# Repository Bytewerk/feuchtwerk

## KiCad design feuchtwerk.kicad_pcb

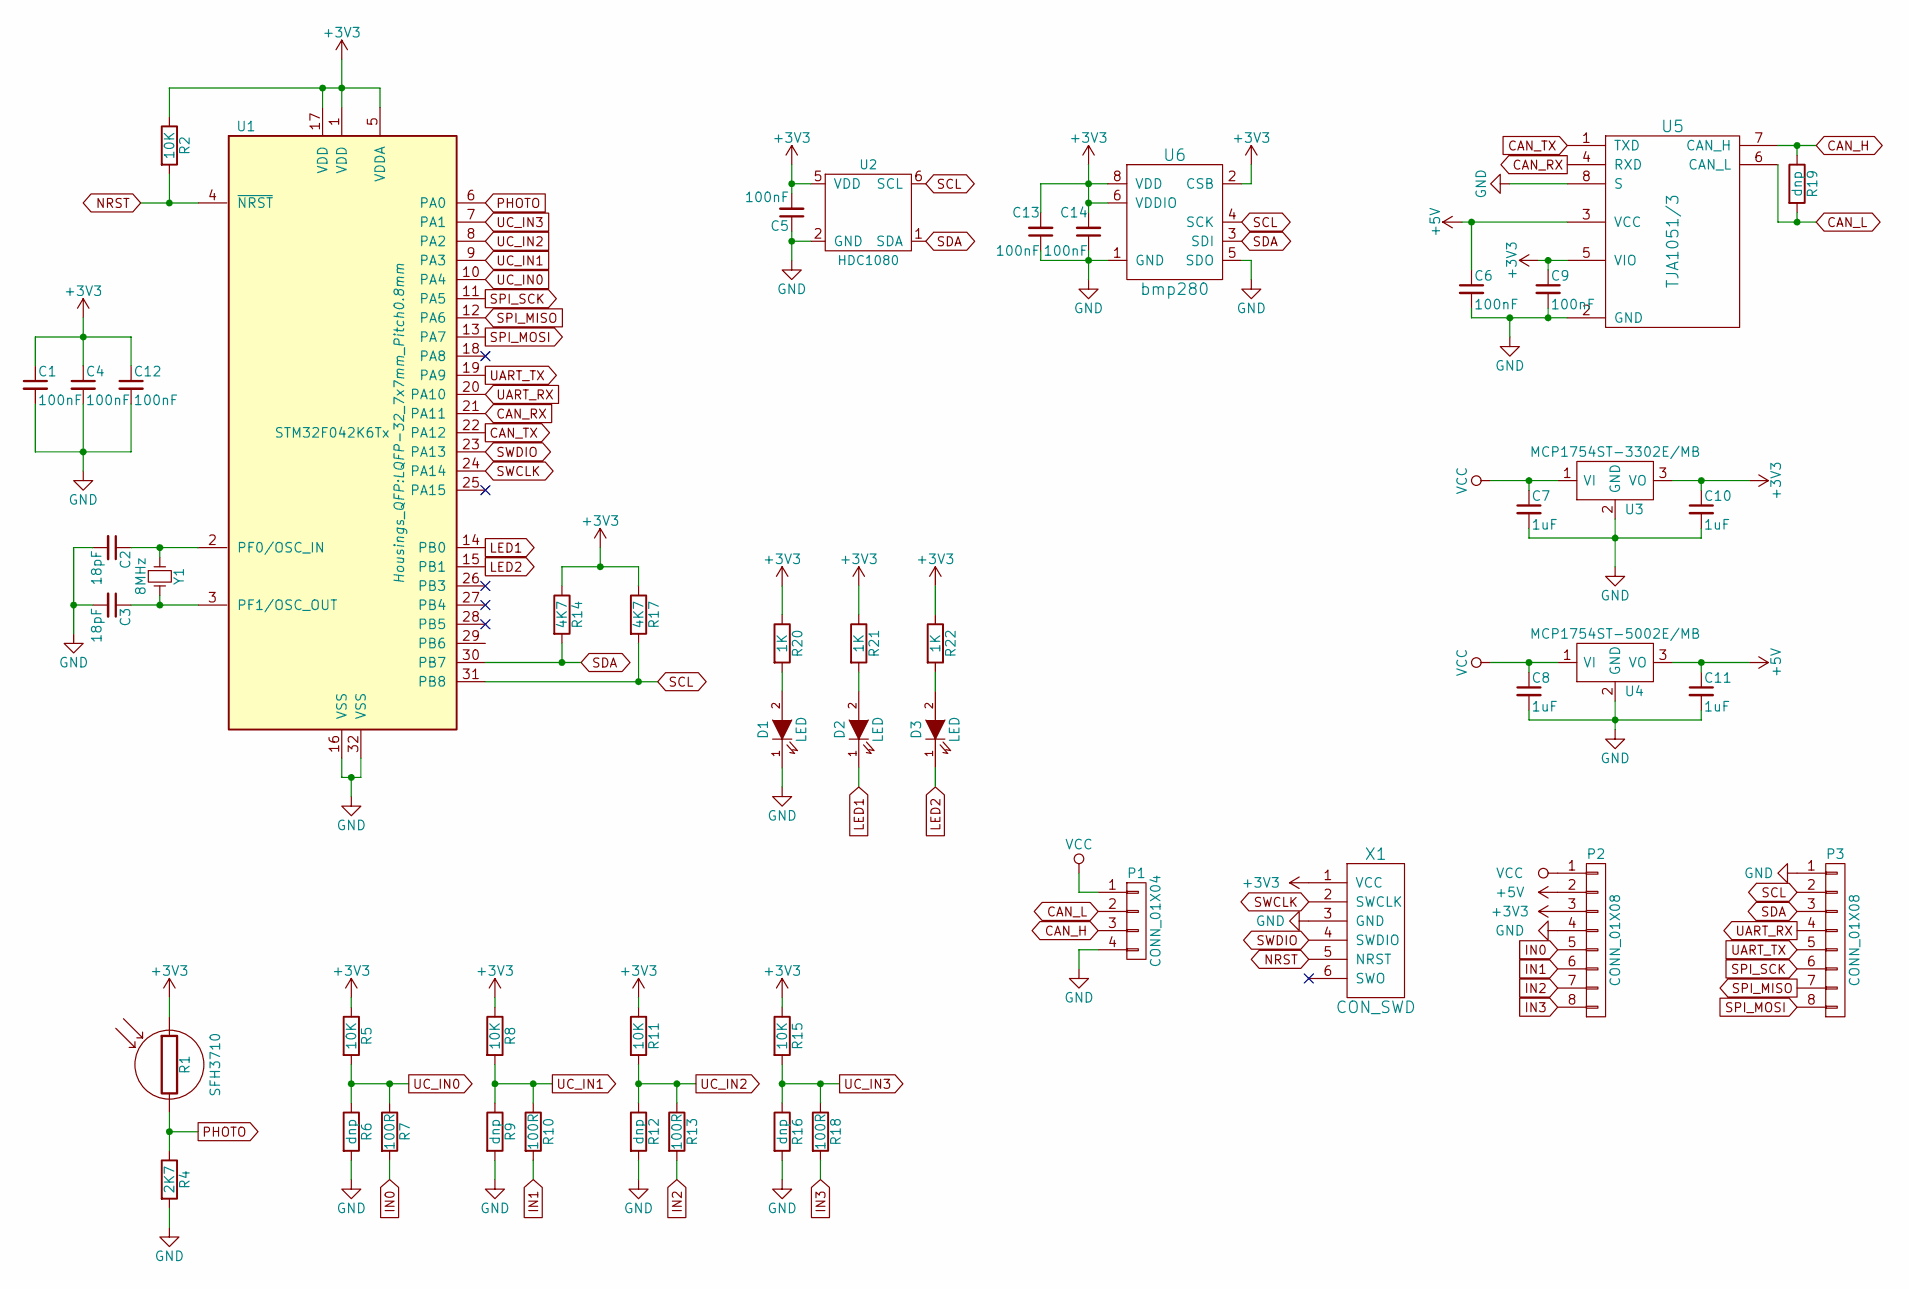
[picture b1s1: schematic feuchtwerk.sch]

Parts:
C1, C4, C5, C6, C9, C12, C13, C14: 100nF; C_0603
C2, C3: 18pF; C_0603
C7, C8, C10, C11: 1uF; C_0603
D1, D2, D3: LED; LED_0603
P1: CONN_01X04; Pin_Header_Straight_1x04
P2, P3: CONN_01X08; Pin_Header_Straight_1x08
R1: SFH3710; R_1206
R2, R5, R8, R11, R15: 10K; R_0603
R4: 2K7; R_0603
R6, R9, R12, R16: dnp; R_0603
R7, R10, R13, R18: 100R; R_0603
R14, R17: 4K7; R_0603
R19: dnp; R_0805
R20, R21, R22: 1K; R_0603
U1: STM32F042K6Tx; LQFP-32_7x7mm_Pitch0.8mm
U2: HDC1080; TEXAS-S-PWSON-N6
U3: MCP1754ST-3302E/MB; SOT89-3_Housing
U4: MCP1754ST-5002E/MB; SOT89-3_Housing
U5: TJA1051/3; SOIC-8_3.9x4.9mm_Pitch1.27mm
U6: bmp280
X1: CON_SWD; TC2030-NL
Y1: 8MHz; ABM3

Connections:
+3V3: C1.1, C4.1, C5.2, C9.1, C10.1, C12.1, C13.2, C14.2, P2.3, R1.1, R2.1, R5.1, R8.1, R11.1, R14.1, R15.1, R17.1, R20.1, R21.1, R22.1, U1.1 (VDD), U1.5 (VDDA), U1.17 (VDD), U2.5 (VDD), U3.3 (VO), U5.5 (VIO), U6.2 (CSB), U6.6 (VDDIO), U6.8 (VDD), X1.1 (VCC)
+5V: C6.1, C11.1, P2.2, U4.3 (VO), U5.3 (VCC)
CAN_H: P1.3, R19.1, U5.7 (CAN_H)
CAN_L: P1.2, R19.2, U5.6 (CAN_L)
CAN_RX: U1.21 (PA11), U5.4 (RXD)
CAN_TX: U1.22 (PA12), U5.1 (TXD)
GND: C1.2, C2.2, C3.2, C4.2, C5.1, C6.2, C7.2, C8.2, C9.2, C10.2, C11.2, C12.2, C13.1, C14.1, D1.1 (K), P1.4, P2.4, P3.1, R4.2, R6.2, R9.2, R12.2, R16.2, U1.16 (VSS), U1.32 (VSS), U2.2 (GND), U3.2 (GND), U4.2 (GND), U5.2 (GND), U5.8 (S), U6.1 (GND), U6.5 (SDO), U6.7 (GND), X1.3 (GND)
IN0: P2.5, R7.2
IN1: P2.6, R10.2
IN2: P2.7, R13.2
IN3: P2.8, R18.2
LED1: D2.1 (K), U1.14 (PB0)
LED2: D3.1 (K), U1.15 (PB1)
NRST: R2.2, U1.4 (~NRST), X1.5 (NRST)
unnamed: C2.1, U1.2 (PF0/OSC_IN), Y1.1
unnamed: C3.1, U1.3 (PF1/OSC_OUT), Y1.2
unnamed: D1.2 (A), R20.2
unnamed: D2.2 (A), R21.2
unnamed: D3.2 (A), R22.2
PHOTO: R1.2, R4.1, U1.6 (PA0)
SCL: P3.2, R17.2, U1.31 (PB8), U2.6 (SCL), U6.4 (SCK)
SDA: P3.3, R14.2, U1.30 (PB7), U2.1 (SDA), U6.3 (SDI)
SPI_MISO: P3.7, U1.12 (PA6)
SPI_MOSI: P3.8, U1.13 (PA7)
SPI_SCK: P3.6, U1.11 (PA5)
SWCLK: U1.24 (PA14), X1.2 (SWCLK)
SWDIO: U1.23 (PA13), X1.4 (SWDIO)
UART_RX: P3.4, U1.20 (PA10)
UART_TX: P3.5, U1.19 (PA9)
UC_IN0: R5.2, R6.1, R7.1, U1.10 (PA4)
UC_IN1: R8.2, R9.1, R10.1, U1.9 (PA3)
UC_IN2: R11.2, R12.1, R13.1, U1.8 (PA2)
UC_IN3: R15.2, R16.1, R18.1, U1.7 (PA1)
VCC: C7.1, C8.1, P1.1, P2.1, U3.1 (VI), U4.1 (VI)

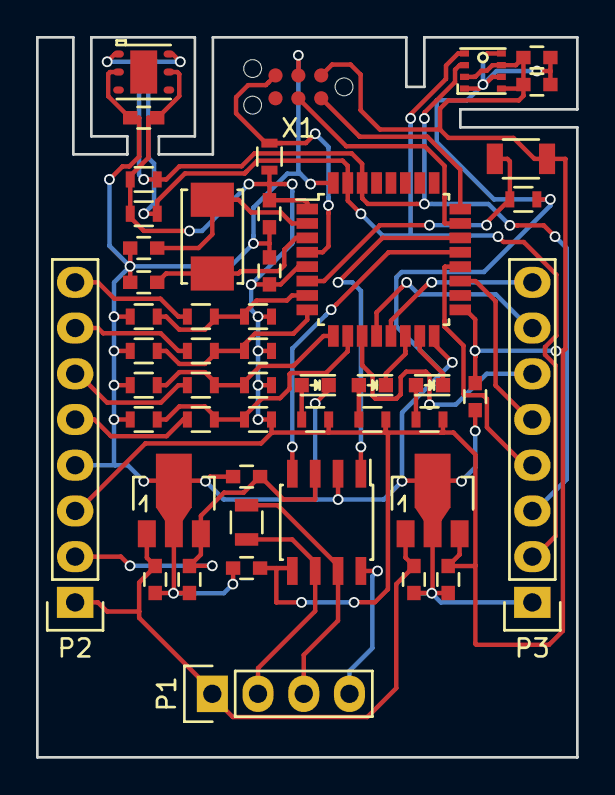
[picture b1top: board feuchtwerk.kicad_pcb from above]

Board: 2 copper layers, 30.0 x 40.0 mm, 49 parts (0 on the bottom side), 34 nets.

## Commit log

2016-06-04 initial checkin
2016-06-05 change board dimensions, milling slot for humidity sensor
2016-06-05 add clearance around tagconnect drills
2016-06-05 add fiducials
2016-06-05 gerber export for fusionpcb
2016-06-14 add exports
2016-06-14 fix wrong light transistor setup, add bmp280 air pressure sensor
2016-10-01 modified HDC1080 symbol; changed pin6 (SCL) type from power to bidirectional
